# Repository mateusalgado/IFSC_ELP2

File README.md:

# IFSC – Eletrônica de Potência II (EPO II) – 2026-2

Aluno: Mateus Salgado Barboza Costa · Prof. Joabel Moia · Engenharia Eletrônica, IFSC Florianópolis.

| Pasta | Conteúdo | Entrega |
|---|---|---|
| `00_Disciplina/` | enunciados do projeto semestral e da Tarefa Extra (os slides das aulas e o plano de ensino ficam só na cópia local, fora do git) | — |
| `Tarefa_01_Calculo_Termico_Dissipador/` | Buck: perdas, cálculo térmico e escolha de dissipador (PSIM, SMath, Python) | `RELATORIO_MATEUS_SALGADO_TAREFA1.pdf` |
| `Tarefa_02_Projeto_Conversor_Estatico/` | Buck: metodologia da Aula 03, escolha de semicondutores e capacitor, perdas | `RELATORIO_MATEUS_SALGADO_TAREFA2.pdf` |
| `Tarefa_03_Projeto_Indutor_Alta_Frequencia/` | indutor toroidal de alta frequência (SMath, planilha Magnetics) | `RELATORIO_MATEUS_SALGADO_TAREFA3.pdf` |
| `Projeto_Flyback/` | **Projeto semestral (Tema II):** fonte flyback 12 V / 3 A, entrada universal, UC3845 — cálculos, simulação LTspice, esquemático e placa KiCad, BOM, relatório, apresentação, guia de montagem e protótipo (Possibilidade II). Revisão B vigente; revisão A completa em `revisoes/RevA_2026-10-19/` | `06_Relatorio/RELATORIO_MATEUS_SALGADO_PROJETO.pdf`, `07_Apresentacao/APRESENTACAO_MATEUS_SALGADO_PROJETO.pdf` |

Índice detalhado do projeto, resultados e comandos de regeneração: [`Projeto_Flyback/README.md`](Projeto_Flyback/README.md).

Os resultados brutos do LTspice (`.raw`, 11 GB) não ficam no repositório: estão em `C:\Users\mateu\ELP2_sim_runs` e são regenerados por `Projeto_Flyback/03_Simulacao/executa_b.py`.

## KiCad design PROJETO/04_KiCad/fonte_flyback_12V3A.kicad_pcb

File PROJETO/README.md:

# Projeto Semestral EPO II 2026-2 – Fonte flyback 12 V / 3 A, entrada universal, UC3845 (Tema II)

Aluno: Mateus Salgado Barboza Costa · Prof. Joabel Moia · IFSC · Entrega/apresentação: **21/12/2026**

## Entregáveis principais

| O quê | Onde |
|---|---|
| **Relatório** (6 seções do plano de ensino, 20 páginas) | `06_Relatorio/RELATORIO_VISUAL.pdf` (fonte: `RELATORIO.md`, tabelas em `tabelas/`, `build.py`) |
| **Apresentação** (14 slides) | `07_Apresentacao/slides.pdf` (`slides.html`) |
| Especificação e aplicações | `01_Especificacao/requisitos.md` |
| Cálculos teóricos (scripts + resultados + figuras) | `02_Calculos/*.py`, `resultados/RESULTADOS_TEORIA.md`, `resultados/*.json`, `assets/*.png` |
| Simulação LTspice (20 casos, medidas, 60 figuras) | `03_Simulacao/` (`gera_netlist.py`, `roda.py`, `plota.py`, `runs/medidas.json`, `analise/*.png`, `PSIM_OPCIONAL.md`) |
| Esquemático KiCad 10 (ERC 0) | `04_KiCad/fonte_flyback_12V3A.kicad_sch`, `fonte_flyback_12V3A_esquematico.pdf` |
| Layout (DRC 0 erros, 0 não conectados, paridade OK) | `04_KiCad/fonte_flyback_12V3A.kicad_pcb`, `gerbers/`, `imagens/`, `3d/`, `VERIFICACAO_LAYOUT.md` |
| BOM com part numbers e custo (1 e 100 un., PCI incluída) | `05_BOM_Custo/BOM.xlsx`, `custo.xlsx`, `custo.md` (`bom.py`) |
| Guia de montagem e ensaio (decisão montar / não montar) | `08_Montagem/GUIA_MONTAGEM.md` |
| Tarefa Extra (modelo com os 13 itens; depende de fotos) | `09_Tarefa_Extra/RELATORIO_TAREFA_EXTRA.md` |

## Resultados em uma linha

12 V / 3 A, 90–264 VAC, 65 kHz, MCD; STP13N65M2 + STPS20H100CT; trafo E-30/7 42:7:9, Lp 294 µH; Vo sim. 12,07–12,08 V, ondulação < 4 mV, Vds máx 482 V (74 %), η 83–85,5 %, MF 99°; placa 140 × 90 mm 2 camadas; custo US$ 39,78 (1 un.) / 20,63 (100 un.).

## Checklist do enunciado (Possibilidade I)

| Item | Estado | Onde |
|---|---|---|
| Requisitos do projeto | ✔ | relatório §4.1, `01_Especificacao` |
| Aplicações | ✔ | relatório §1 |
| Levantamento das características elétricas | ✔ | §4.1–4.2, `02_Calculos` |
| Simulação do conversor | ✔ | §4.6, `03_Simulacao` |
| Esquemático | ✔ | §4.7, `04_KiCad` |
| Projeto físico do transformador | ✔ | §4.2, `transformador.py` |
| Escolha dos capacitores | ✔ | §4.3, `saida.py`, `entrada.py` |
| Escolha dos diodos | ✔ | §4.4 |
| Componentes associados ao CI | ✔ | §4.5, `uc3845.py`, `compensador.py` |
| Escolha do driver | ✔ | §4.5 (saída totem-pole do UC3845) |
| Transistor: perdas e dissipador | ✔ | §4.4, `semicondutores.py` |
| Lista de materiais com part number e custo (com PCI) | ✔ | §4.8, `05_BOM_Custo` |
| Layout da PCI (potência + comando) | ✔ | §4.9, `04_KiCad` |
| Relatório nas 6 seções | ✔ | `06_Relatorio` |
| Apresentação | ✔ | `07_Apresentacao` |
| Tarefa Extra | ☐ modelo pronto; **faltam as fotos do produto comercial** (obrigatória só na Possibilidade I) |
| Protótipo (Possibilidade II) | ☐ opcional; guia e critérios em `08_Montagem` |

## Decisão pendente do aluno

1. **Montar ou não o protótipo** (ver `08_Montagem/GUIA_MONTAGEM.md` §1: custo ≈ R$ 220, prazo 3–4 semanas, precisa de isolador/variac e sonda diferencial).
2. Se não montar: fotografar um produto comercial e preencher `09_Tarefa_Extra/RELATORIO_TAREFA_EXTRA.md`.
3. Conferir os preços da BOM no distribuidor antes de comprar (referências de out/2026) e a disponibilidade do STP13N65M2 (substitutos listados).

## Como regenerar tudo

```bash
# teoria (WSL)
wsl -d Ubuntu -- bash -c 'cd /mnt/c/.../PROJETO/02_Calculos && python3 run_all.py'
# simulação (gera netlists, roda LTspice em lote, plota)
wsl -d Ubuntu -- bash -c 'cd /mnt/c/.../PROJETO/03_Simulacao && python3 gera_netlist.py && python3 roda.py && python3 plota.py'
# KiCad: esquemático → ERC/netlist → placement → roteador → placa → DRC → exportações
wsl -d Ubuntu -- bash -c 'cd /mnt/c/.../PROJETO/04_KiCad && python3 gera_sch.py && python3 placement.py && python3 router.py'
"C:\Program Files\KiCad\10.0\bin\python.exe" 04_KiCad\gera_pcb.py
"C:\Program Files\KiCad\10.0\bin\kicad-cli.exe" pcb drc --severity-all --schematic-parity --refill-zones --save-board 04_KiCad\fonte_flyback_12V3A.kicad_pcb
# BOM, tabelas e relatório
wsl -d Ubuntu -- bash -c 'cd /mnt/c/.../PROJETO/05_BOM_Custo && python3 bom.py; cd ../06_Relatorio && python3 gera_tabelas.py'
"C:\Program Files\KiCad\10.0\bin\python.exe" 06_Relatorio\build.py
```

Ferramentas: Python 3 (numpy, matplotlib) no WSL Ubuntu; LTspice XVII; KiCad 10 (kicad-cli, pcbnew); pandoc; Chrome headless (PDF); LibreOffice (xlsx).

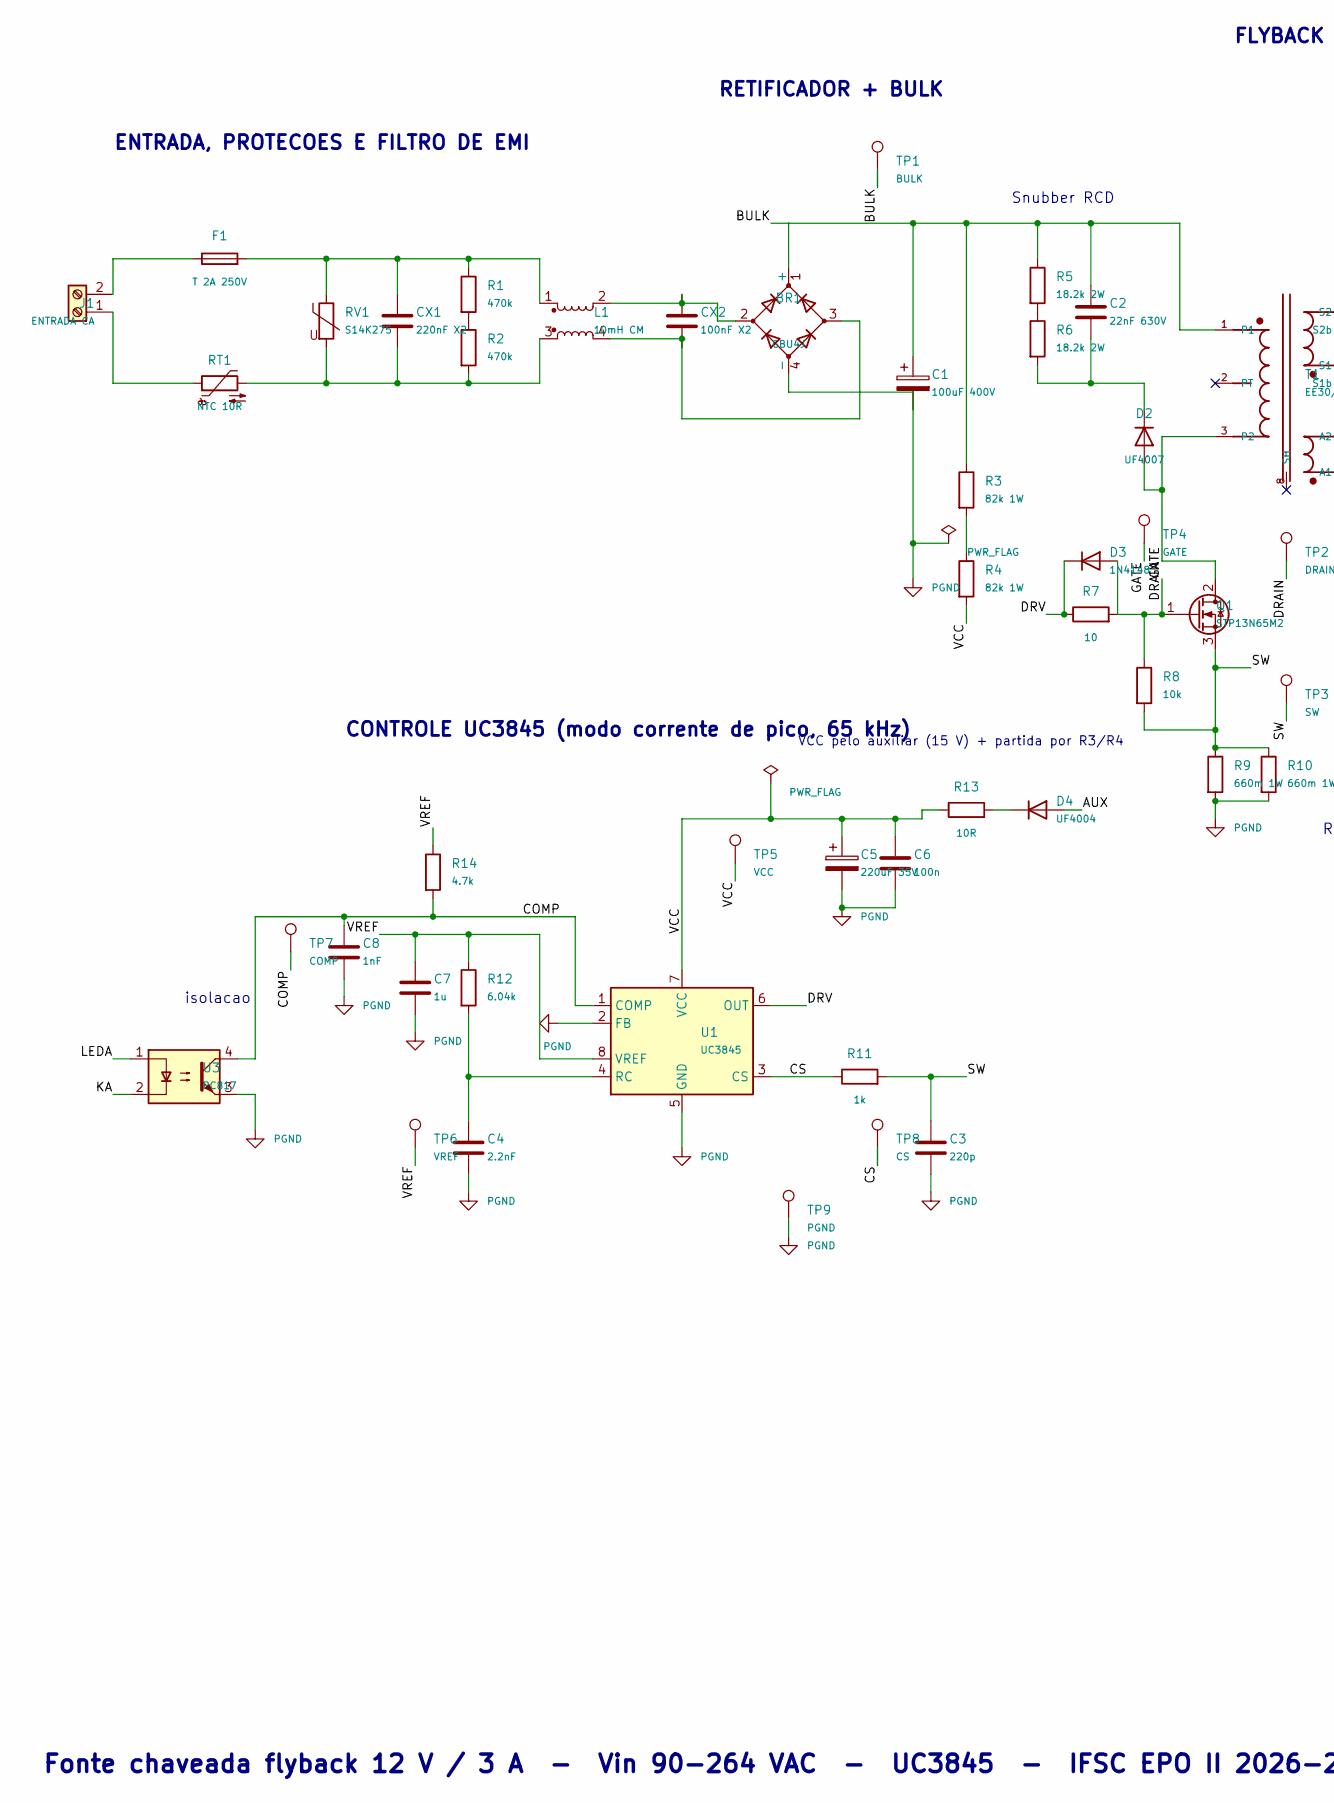
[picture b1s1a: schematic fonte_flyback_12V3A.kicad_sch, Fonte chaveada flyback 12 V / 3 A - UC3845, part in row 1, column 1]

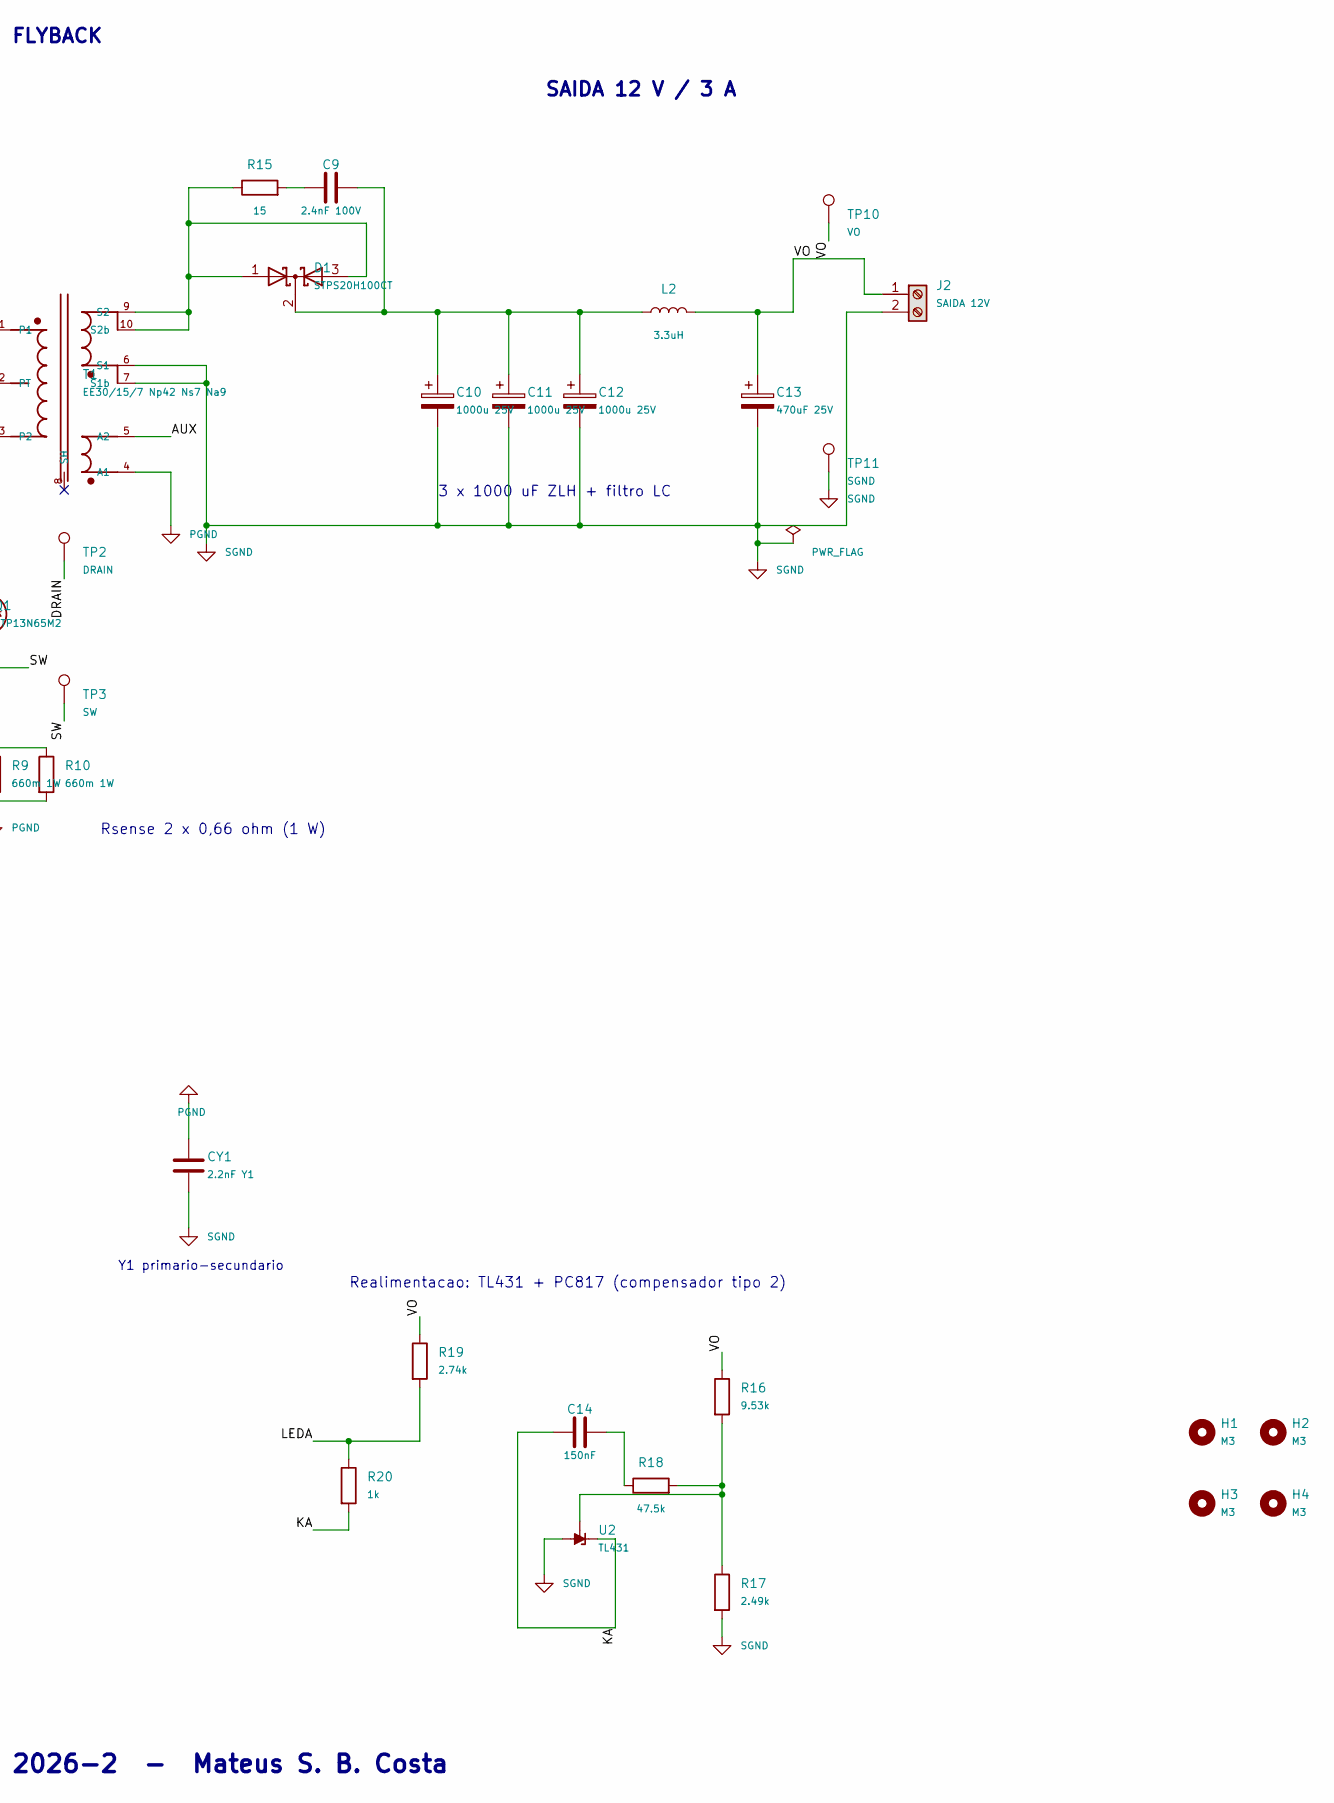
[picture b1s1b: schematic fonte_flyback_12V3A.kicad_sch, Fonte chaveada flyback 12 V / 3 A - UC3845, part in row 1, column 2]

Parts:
BR1: GBU4J; Diode_Bridge_Vishay_GBU
C1: 100uF 400V; CP_Radial_D16.0mm_P7.50mm
C2: 22nF 630V; C_Disc_D7.5mm_W5.0mm_P10.00mm
C3: 220p; C_Disc_D5.0mm_W2.5mm_P5.00mm
C4: 2.2nF; C_Disc_D5.0mm_W2.5mm_P5.00mm
C5: 220uF 35V; CP_Radial_D8.0mm_P3.50mm
C6: 100n; C_Disc_D5.0mm_W2.5mm_P5.00mm
C7: 1u; C_Disc_D5.0mm_W2.5mm_P5.00mm
C8: 1nF; C_Disc_D5.0mm_W2.5mm_P5.00mm
C9: 2.4nF 100V; C_Rect_L7.0mm_W2.5mm_P5.00mm
C10, C11, C12: 1000u 25V; CP_Radial_D10.0mm_P5.00mm
C13: 470uF 25V; CP_Radial_D10.0mm_P5.00mm
C14: 150nF; C_Disc_D5.0mm_W2.5mm_P5.00mm
CX1: 220nF X2; C_Rect_L18.0mm_W8.0mm_P15.00mm_FKS3_FKP3
CX2: 100nF X2; C_Rect_L18.0mm_W8.0mm_P15.00mm_FKS3_FKP3
CY1: 2.2nF Y1; C_Disc_D9.0mm_W5.0mm_P10.00mm
D1: STPS20H100CT; TO-220-3_Vertical
D2: UF4007; D_DO-41_SOD81_P10.16mm_Horizontal
D3: 1N4148; D_DO-35_SOD27_P7.62mm_Horizontal
D4: UF4004; D_DO-41_SOD81_P10.16mm_Horizontal
F1: T 2A 250V; Fuseholder_Cylinder-5x20mm_Stelvio-Kontek_PTF78_Horizontal_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
H1, H2, H3, H4: M3; MountingHole_3.2mm_M3
J1: ENTRADA CA; TerminalBlock_Phoenix_MKDS-1,5-2-5.08_1x02_P5.08mm_Horizont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
J2: SAIDA 12V; TerminalBlock_Phoenix_MKDS-1,5-2-5.08_1x02_P5.08mm_Horizont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
L1: 10mH CM; L_CM_WE-CMB-XS
L2: 3.3uH; L_Radial_D7.0mm_P3.00mm
Q1: STP13N65M2; TO-220-3_Vertical
R1, R2: 470k; R_Axial_DIN0207_L6.3mm_D2.5mm_P10.16mm_Horizontal
R3, R4: 82k 1W; R_Axial_DIN0411_L9.9mm_D3.6mm_P12.70mm_Horizontal
R5, R6: 18.2k 2W; R_Axial_DIN0414_L11.9mm_D4.5mm_P15.24mm_Horizontal
R7: 10; R_Axial_DIN0207_L6.3mm_D2.5mm_P10.16mm_Horizontal
R8: 10k; R_Axial_DIN0207_L6.3mm_D2.5mm_P10.16mm_Horizontal
R9, R10: 660m 1W; R_Axial_DIN0411_L9.9mm_D3.6mm_P12.70mm_Horizontal
R11, R20: 1k; R_Axial_DIN0207_L6.3mm_D2.5mm_P10.16mm_Horizontal
R12: 6.04k; R_Axial_DIN0207_L6.3mm_D2.5mm_P10.16mm_Horizontal
R13: 10R; R_Axial_DIN0207_L6.3mm_D2.5mm_P10.16mm_Horizontal
R14: 4.7k; R_Axial_DIN0207_L6.3mm_D2.5mm_P10.16mm_Horizontal
R15: 15; R_Axial_DIN0207_L6.3mm_D2.5mm_P10.16mm_Horizontal
R16: 9.53k; R_Axial_DIN0207_L6.3mm_D2.5mm_P10.16mm_Horizontal
R17: 2.49k; R_Axial_DIN0207_L6.3mm_D2.5mm_P10.16mm_Horizontal
R18: 47.5k; R_Axial_DIN0207_L6.3mm_D2.5mm_P10.16mm_Horizontal
R19: 2.74k; R_Axial_DIN0207_L6.3mm_D2.5mm_P10.16mm_Horizontal
RT1: NTC 10R; C_Disc_D9.0mm_W5.0mm_P7.50mm
RV1: S14K275; RV_Disc_D12mm_W4.2mm_P7.5mm
T1: EE30/15/7 Np42 Ns7 Na9; Trafo_EE30_10pin
TP1: BULK; TestPoint_THTPad_D2.0mm_Drill1.0mm
TP2: DRAIN; TestPoint_THTPad_D2.0mm_Drill1.0mm
TP3: SW; TestPoint_THTPad_D2.0mm_Drill1.0mm
TP4: GATE; TestPoint_THTPad_D2.0mm_Drill1.0mm
TP5: VCC; TestPoint_THTPad_D2.0mm_Drill1.0mm
TP6: VREF; TestPoint_THTPad_D2.0mm_Drill1.0mm
TP7: COMP; TestPoint_THTPad_D2.0mm_Drill1.0mm
TP8: CS; TestPoint_THTPad_D2.0mm_Drill1.0mm
TP9: PGND; TestPoint_THTPad_D2.0mm_Drill1.0mm
TP10: VO; TestPoint_THTPad_D2.0mm_Drill1.0mm
TP11: SGND; TestPoint_THTPad_D2.0mm_Drill1.0mm
U1: UC3845; DIP-8_W7.62mm
U2: TL431; TO-92_Inline_Wide
U3: PC817; DIP-4_W7.62mm

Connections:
/AUX: D4.2 (A), T1.5 (A2)
/BULK: BR1.1 (+), C1.1, C2.1, R3.1, R5.1, T1.1, TP1.1
/COMP: C8.1, R14.2, TP7.1, U1.1 (COMP), U3.4
/CS: R11.1, TP8.1, U1.3 (CS)
/DRAIN: D2.2 (A), Q1.2 (D), T1.3 (P2), TP2.1
/DRV: D3.1 (K), R7.1, U1.6 (OUT)
/GATE: D3.2 (A), Q1.1 (G), R7.2, R8.1, TP4.1
/KA: C14.1, R20.2, U2.3 (K), U3.2
/LEDA: R19.2, R20.1, U3.1
/SW: C3.1, Q1.3 (S), R8.2, R9.1, R10.1, R11.2, TP3.1
/VCC: C5.1, C6.1, R4.2, R13.1, TP5.1, U1.7 (VCC)
/VO: C13.1, J2.1, L2.2, R16.1, R19.1, TP10.1
/VREF: C7.1, R12.1, R14.1, TP6.1, U1.8 (VREF)
unnamed: BR1.2, CX2.1, L1.2
unnamed: BR1.3, CX2.2, L1.4
unnamed: C9.1, R15.2
unnamed: C14.2, R18.1
unnamed: CX1.1, F1.2, L1.1, R1.1, RV1.1
unnamed: CX1.2, L1.3, R2.2, RT1.2, RV1.2
unnamed: C9.2, C10.1, C11.1, C12.1, D1.2 (K), L2.1
unnamed: C2.2, D2.1 (K), R6.2
unnamed: D4.1 (K), R13.2
unnamed: J1.1, RT1.1
unnamed: F1.1, J1.2
unnamed: R1.2, R2.1
unnamed: R3.2, R4.1
unnamed: R5.2, R6.1
unnamed: D1.1 (A), D1.3 (A), R15.1, T1.9 (S2), T1.10 (S2b)
unnamed: C4.1, R12.2, U1.4 (RC)
unnamed: R16.2, R17.1, R18.2, U2.1 (REF)
PGND: BR1.4 (-), C1.2, C3.2, C4.2, C5.2, C6.2, C7.2, C8.2, CY1.1, R9.2, R10.2, T1.4 (A1), TP9.1, U1.2 (FB), U1.5 (GND), U3.3
SGND: C10.2, C11.2, C12.2, C13.2, CY1.2, J2.2, R17.2, T1.6 (S1), T1.7 (S1b), TP11.1, U2.2 (A)

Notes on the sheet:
Snubber RCD
Rsense 2 x 0,66 ohm (1 W)
3 x 1000 uF ZLH + filtro LC
isolacao
VCC pelo auxiliar (15 V) + partida por R3/R4
Realimentacao: TL431 + PC817 (compensador tipo 2)
Y1 primario-secundario
ENTRADA, PROTECOES E FILTRO DE EMI
RETIFICADOR + BULK
FLYBACK
SAIDA 12 V / 3 A
CONTROLE UC3845 (modo corrente de pico, 65 kHz)
Fonte chaveada flyback 12 V / 3 A - Vin 90-264 VAC - UC3845 - IFSC EPO II 2026-2 - Mateus S. B. Costa

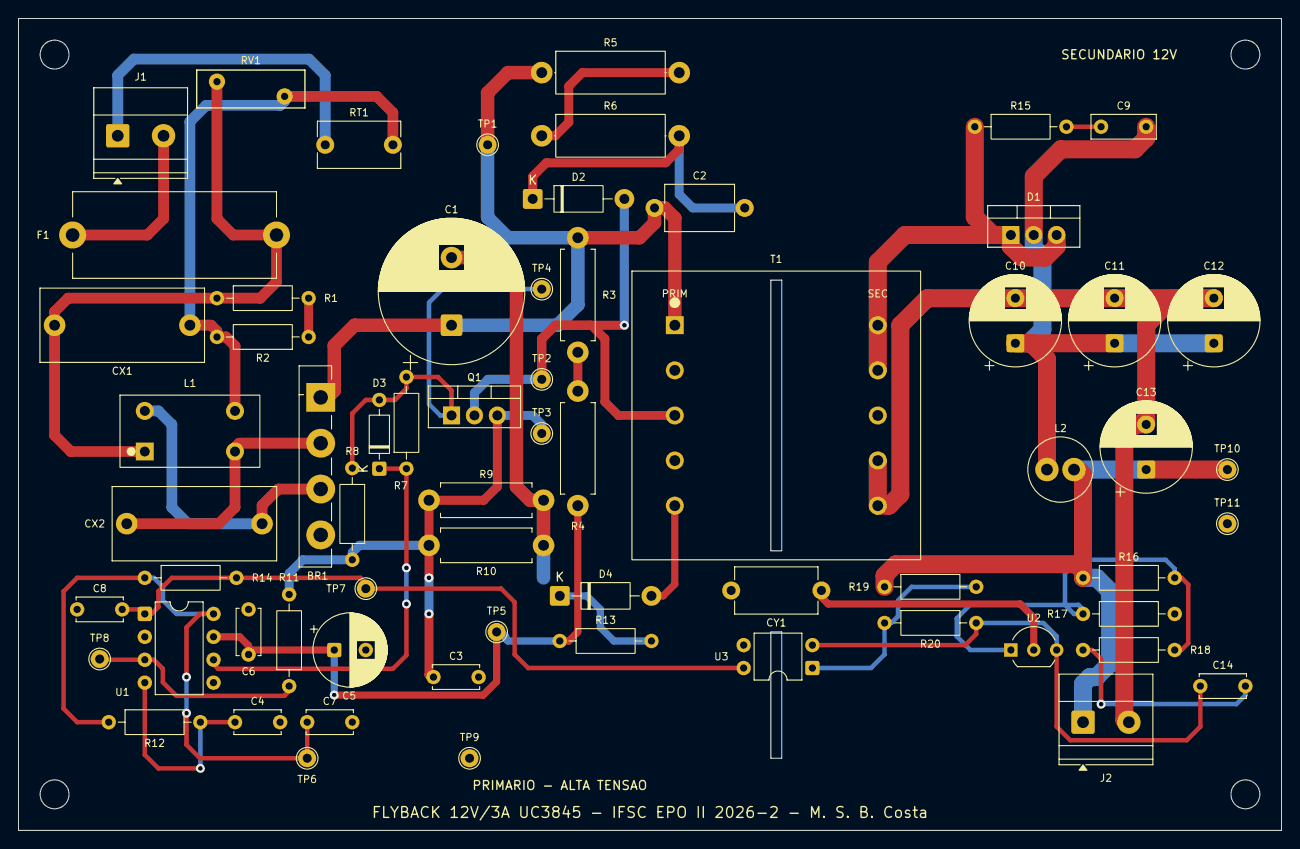
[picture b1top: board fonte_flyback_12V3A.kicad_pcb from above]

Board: 2 copper layers, 140.0 x 90.0 mm, 69 parts (0 on the bottom side), 32 nets.

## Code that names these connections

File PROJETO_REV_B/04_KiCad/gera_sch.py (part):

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    r7a, r7b = P("R7", 1), P("R7", 2)
    d3k, d3a = P("D3", 1), P("D3", 2)
    s.wire(r7b, qg); s.junction(qg)
    s.wire(r7a, (r7a[0] - 2.54, r7a[1])); s.label("DRV", (r7a[0] - 2.54, r7a[1]), 180)
    s.wire(d3k, (r7a[0], d3k[1]), r7a); s.wire(d3a, (r7b[0], d3a[1]), r7b); s.junction(r7a)
    r8a, r8b = P("R8", 1), P("R8", 2)
    s.wire(r8a, (r8a[0], qg[1])); s.junction((r8a[0], qg[1]))
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    s.wire((qs[0], 120.65), r9a); s.wire(r9a, (r10a[0], r9a[1]), r10a); s.junction(r9a)
    s.wire(r9b, (r10b[0], r9b[1]), r10b); s.junction(r9b)
    s.wire(r9b, (r9b[0], r9b[1] + 2.54)); s.power("PGND", r9b[0], r9b[1] + 2.54)
    s.wire(qg, (qg[0], qg[1] - 5.08)); s.label("GATE", (qg[0], qg[1] - 5.08), 90)
    s.text("Rsense 2 x 0,66 ohm (1 W)", 203.2, 135.89, 1.5)
    s.text("JP1/JP2: lacos de fio para sonda de corrente (Aula 08)", 20.32, 45.72, 1.3)
    # ---------------------------------------------------------------- SECUNDARIO
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    s.wire(t1s1, (sgx, t1s1[1])); s.wire(t1s1b, (sgx, t1s1b[1])); s.junction((sgx, t1s1b[1]))
    s.wire((sgx, t1s1[1]), (sgx, 91.44)); s.junction((sgx, 91.44))
    s.wire((sgx, 91.44), (sgx, 93.98)); s.power("SGND", sgx, 93.98)
    # auxiliar: A2 -> AUX (label), A1 (ponto) -> PGND
    s.wire(t1a2, (t1a2[0] + 5.08, t1a2[1])); s.label("AUX", (t1a2[0] + 5.08, t1a2[1]))
    s.wire(t1a1, (t1a1[0] + 5.08, t1a1[1]), (t1a1[0] + 5.08, 91.44)); s.power("PGND", t1a1[0] + 5.08, 91.44)
    # banco de capacitores + LC + saida
    for ref in ("C10", "C11", "C12"):
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    comp, fbp, cs, rc, gnd, out, vcc, vref = (P("U1", n) for n in ("1", "2", "3", "4", "5", "6", "7", "8"))
    s.wire(gnd, (gnd[0], gnd[1] + 5.08)); s.power("PGND", gnd[0], gnd[1] + 5.08)
    s.wire(fbp, (fbp[0] - 5.08, fbp[1])); s.power("PGND", fbp[0] - 5.08, fbp[1], 270)
    s.wire(out, (out[0] + 5.08, out[1])); s.label("DRV", (out[0] + 5.08, out[1]))
    # VREF: sobe pela esquerda ate y = 149.86 e vai para RT, C_ref e label
    vrefy = 149.86
    r12a, r12b, c4a, c4b = P("R12", 1), P("R12", 2), P("C4", 1), P("C4", 2)
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    s.wire(c8b, (c8b[0], c8b[1] + 2.54)); s.power("PGND", c8b[0], c8b[1] + 2.54)
    s.wire(o4, (50.8, o4[1]), (50.8, compy))
    s.wire(o3, (50.8, o3[1]), (50.8, o3[1] + 5.08)); s.power("PGND", 50.8, o3[1] + 5.08)
    s.wire(o1, (o1[0] - 2.54, o1[1])); s.label("LEDA", (o1[0] - 2.54, o1[1]), 180)
    s.wire(o2, (o2[0] - 2.54, o2[1])); s.label("KA", (o2[0] - 2.54, o2[1]), 180)
    s.label("COMP", (88.9, compy), 0)
    s.text("isolacao", 40.64, 160.02, 1.5)
    # CS: filtro RC
    r11a, r11b, c3a, c3b = P("R11", 1), P("R11", 2), P("C3", 1), P("C3", 2)
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    r13a, r13b, d4k, d4a = P("R13", 1), P("R13", 2), P("D4", 1), P("D4", 2)
    s.wire((146.05, vccy), (146.05, r13a[1]), r13a)
    s.wire(r13b, d4k)
    s.wire(d4a, (d4a[0] + 2.54, d4a[1])); s.label("AUX", (d4a[0] + 2.54, d4a[1]))
    s.text("VCC pelo auxiliar (15 V) + partida por R3/R4", 128.27, 123.19, 1.3)
    # ---------------------------------------------------------------- REALIMENTACAO (fios)
    ra1, ra2, rb1, rb2 = P("R16", 1), P("R16", 2), P("R17", 1), P("R17", 2)
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    rl1, rl2, rbias1, rbias2 = P("R19", 1), P("R19", 2), P("R20", 1), P("R20", 2)
    s.wire(rl1, (rl1[0], rl1[1] - 2.54)); s.label("VO", (rl1[0], rl1[1] - 2.54), 90)
    s.wire(rl2, (rl2[0], 222.25), (rbias1[0], 222.25), rbias1); s.junction((rbias1[0], 222.25))
    s.wire((rbias1[0], 222.25), (rbias1[0] - 5.08, 222.25)); s.label("LEDA", (rbias1[0] - 5.08, 222.25), 180)
    s.wire(rbias2, (rbias2[0], rbias2[1] + 2.54), (rbias2[0] - 5.08, rbias2[1] + 2.54)); s.label("KA", (rbias2[0] - 5.08, rbias2[1] + 2.54), 180)
    s.text("Realimentacao: TL431 + PC817 (compensador tipo 2)", 238.76, 200.66, 1.5)
    # Y cap
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            s.power(nm, p[0], p[1] + 2.54)
        else:
            s.label(nm, (p[0], p[1] + 2.54), 270)
    s.label("DRAIN", (drain_x, 96.52), 270)
    s.label("BULK", (brp[0] - 2.54, bulky), 180)
    s.wire((brp[0], bulky), (brp[0] - 2.54, bulky))
    # textos
    s.text("ENTRADA, PROTECOES E FILTRO DE EMI", 30.48, 38.1, 2.0, True)
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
